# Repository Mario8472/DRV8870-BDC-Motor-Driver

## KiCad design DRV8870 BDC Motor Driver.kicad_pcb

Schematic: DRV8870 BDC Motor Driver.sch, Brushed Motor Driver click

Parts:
C1, C2: 100nF; C_0805_2012Metric
CN1, CN2: PinConnector1x08; Connector1x08_click
D1: LED; LED_0805_2012Metric
IN1, IN2, IN3, IN4: LED; LED_0805_2012Metric
J1: Screw_Terminal_01x06; PCB_Screw_Terminal_5.08_6ways
JMP1: J0805; Jumper_0805
R1, R4, R5, R6, R7: 4k7; R_0805_2012Metric
R2, R3: R; R_1206_3216Metric
U1, U2: DRV8870; HSOP-8
logo1: mikroBUSlogo; mikrobus_logo5

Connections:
+3V3: CN1.7, JMP1.1
+5V: CN2.7, JMP1.3
+BATT: C1.1, C2.1, J1.4, U1.5, U2.5
/IN1: CN1.2, R4.1, U1.2
/IN2: CN1.3, R5.1, U1.3
/IN3: CN2.2, R6.1, U2.2
/IN4: CN2.1, R7.1, U2.3
/OUT1: J1.6, U1.8
/OUT2: J1.5, U1.6
/OUT3: J1.2, U2.8
/OUT4: J1.1, U2.6
GND: C1.2, C2.2, CN1.8, CN2.8, D1.1 (K), IN1.1 (K), IN2.1 (K), IN3.1 (K), IN4.1 (K), J1.3, R2.2, R3.2, U1.1, U1.9, U2.1, U2.9
unnamed: D1.2 (A), R1.2
unnamed: IN1.2 (A), R4.2
unnamed: IN2.2 (A), R5.2
unnamed: IN3.2 (A), R6.2
unnamed: IN4.2 (A), R7.2
unnamed: R2.1, U1.7
unnamed: R3.1, U2.7
VCC: JMP1.2, R1.1, U1.4, U2.4

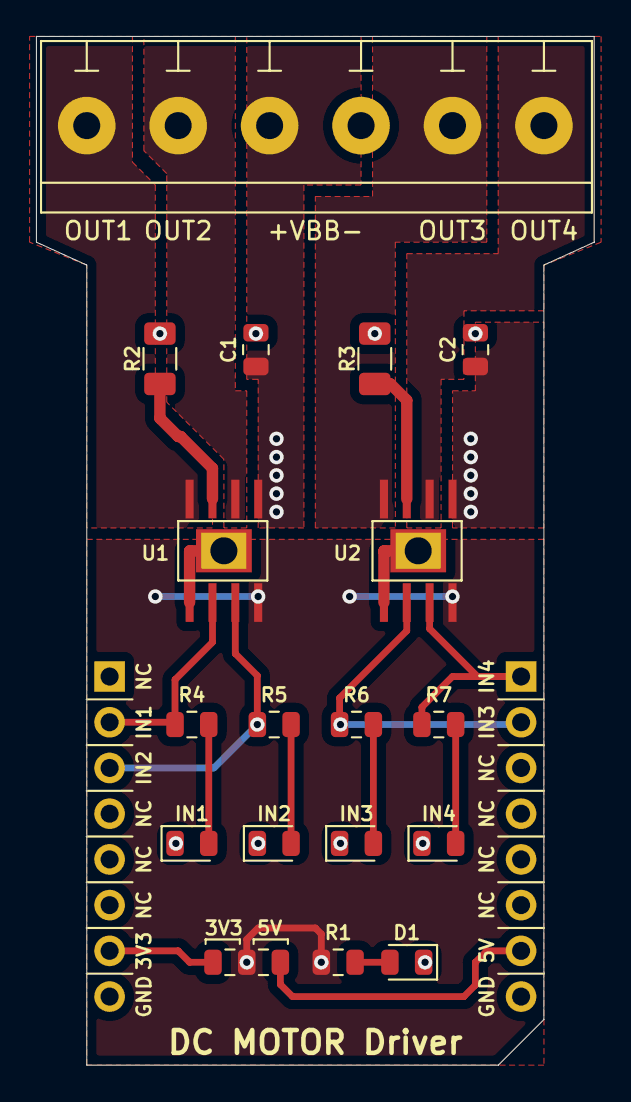
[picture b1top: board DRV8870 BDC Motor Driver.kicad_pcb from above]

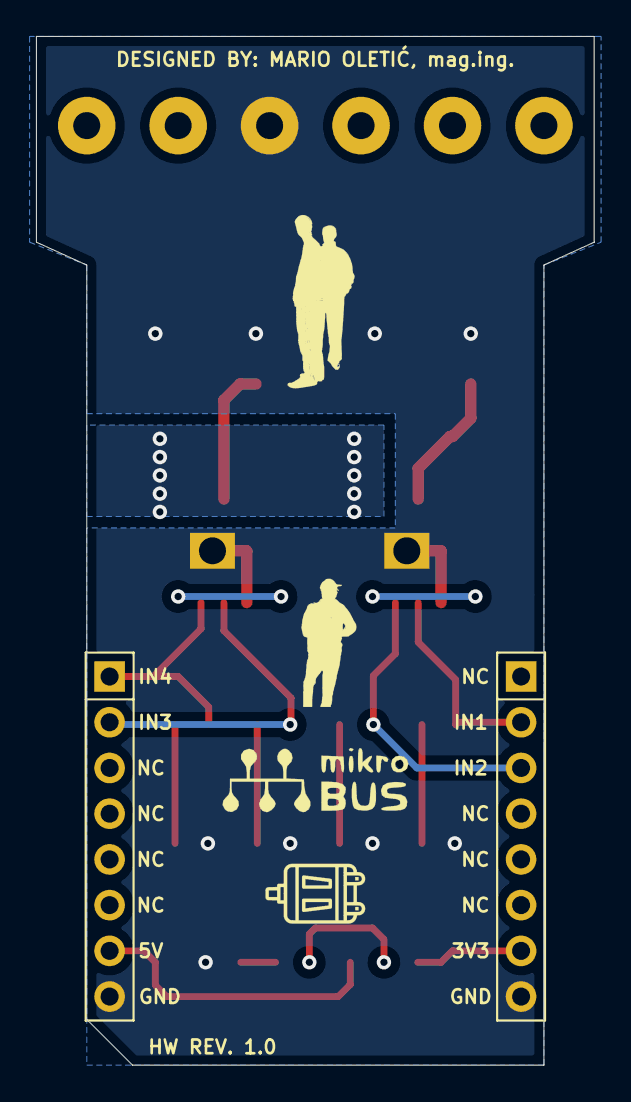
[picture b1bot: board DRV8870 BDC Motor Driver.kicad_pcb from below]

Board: 2 copper layers, 31.0 x 57.2 mm, 21 parts (3 on the bottom side), 20 nets.
